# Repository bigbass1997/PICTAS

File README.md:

### Description
The PICTAS is an input device used to replay Tool-Assisted-Speedruns (aka Tool-Assisted-Superruns) on physical hardware.

A PIC18F47K42 microcontroller is used for the replay portion of the device, and the smaller PIC18F27K42 is used for controlling the input displays.

Unlike a typical TAS replay device, this one stores the TAS inputs on-board, using serial flash memory (W25Q128JVSIQ), capable of storing 16 MB of input data. The advantage is that USB communication is not required during replay. It simplifies the replay process, and greatly reduces the chance of corrupted inputs. Additionally, once programmed, the device can be used without a USB host computer (WIP feature).

This project is still a prototype under heavy development. While I will offer help and support as best I can, please understand that significant code and design changes can occur at any time.

### Usage
The general process looks like this: Load movie into a [host interface](https://github.com/bigbass1997/pictas-interface-rs). Program the movie's inputs and config options onto the PICTAS device. Finally, use one of the available start methods to begin the playback.

Refer to the [PICTAS-Interface project](https://github.com/bigbass1997/pictas-interface-rs) for details on how to use that software. Anyone is free to make their own interface software. There will be docs provided here once the communication protocol has stablized. The PICTAS communicates over USB at a 500,000 baud rate. Single byte commands are initiated from the interface. The PICTAS will respond with one or more bytes.

Because the input data is saved onto the device, you will _not_ need to reprogram it again unless you wish to change the TAS inputs or other configuration data.

### Flash Memory Map
```
0x000000 - 0xFFEFFF | Sequential controller inputs
0xFFF000 - 0xFFF0FF | Config options
0xFFF100 - 0xFFFFFF | Frame-numbered commands
```
All except the last sector (4KB) of memory, is dedicated to storing the TAS inputs. Format will depend on the console and how many controllers are used. Within the last sector, the first 256 bytes are for config options, while the rest is for special commands that are performed on specific frame numbers.

Each command is made up of a 3 byte wide number, which specifies the frame number. And then a 1 byte command.
```
0x00 | Console Reset
0x01 | Console Power off and on

0xFF | Null
```

### Input Displays
This replay device also supports input displays (aka viz/visualization boards), providing the viewers a way see which inputs are being pressed in real time.

The displays are designed to be placed on a SPI bus, where each display board shares the same clock and serial signals. Each device uses it's own Chip Select signal as a data latch.

An auxilary power supply must be connected for these displays. The PCB design is rated for a maximum of 2Amps.

### Discord/Support
If you have questions or suggestions, you can find me on the [N64brew Discord server](https://discord.gg/WqFgNWf) or the [TASBot server](https://discord.tas.bot/).

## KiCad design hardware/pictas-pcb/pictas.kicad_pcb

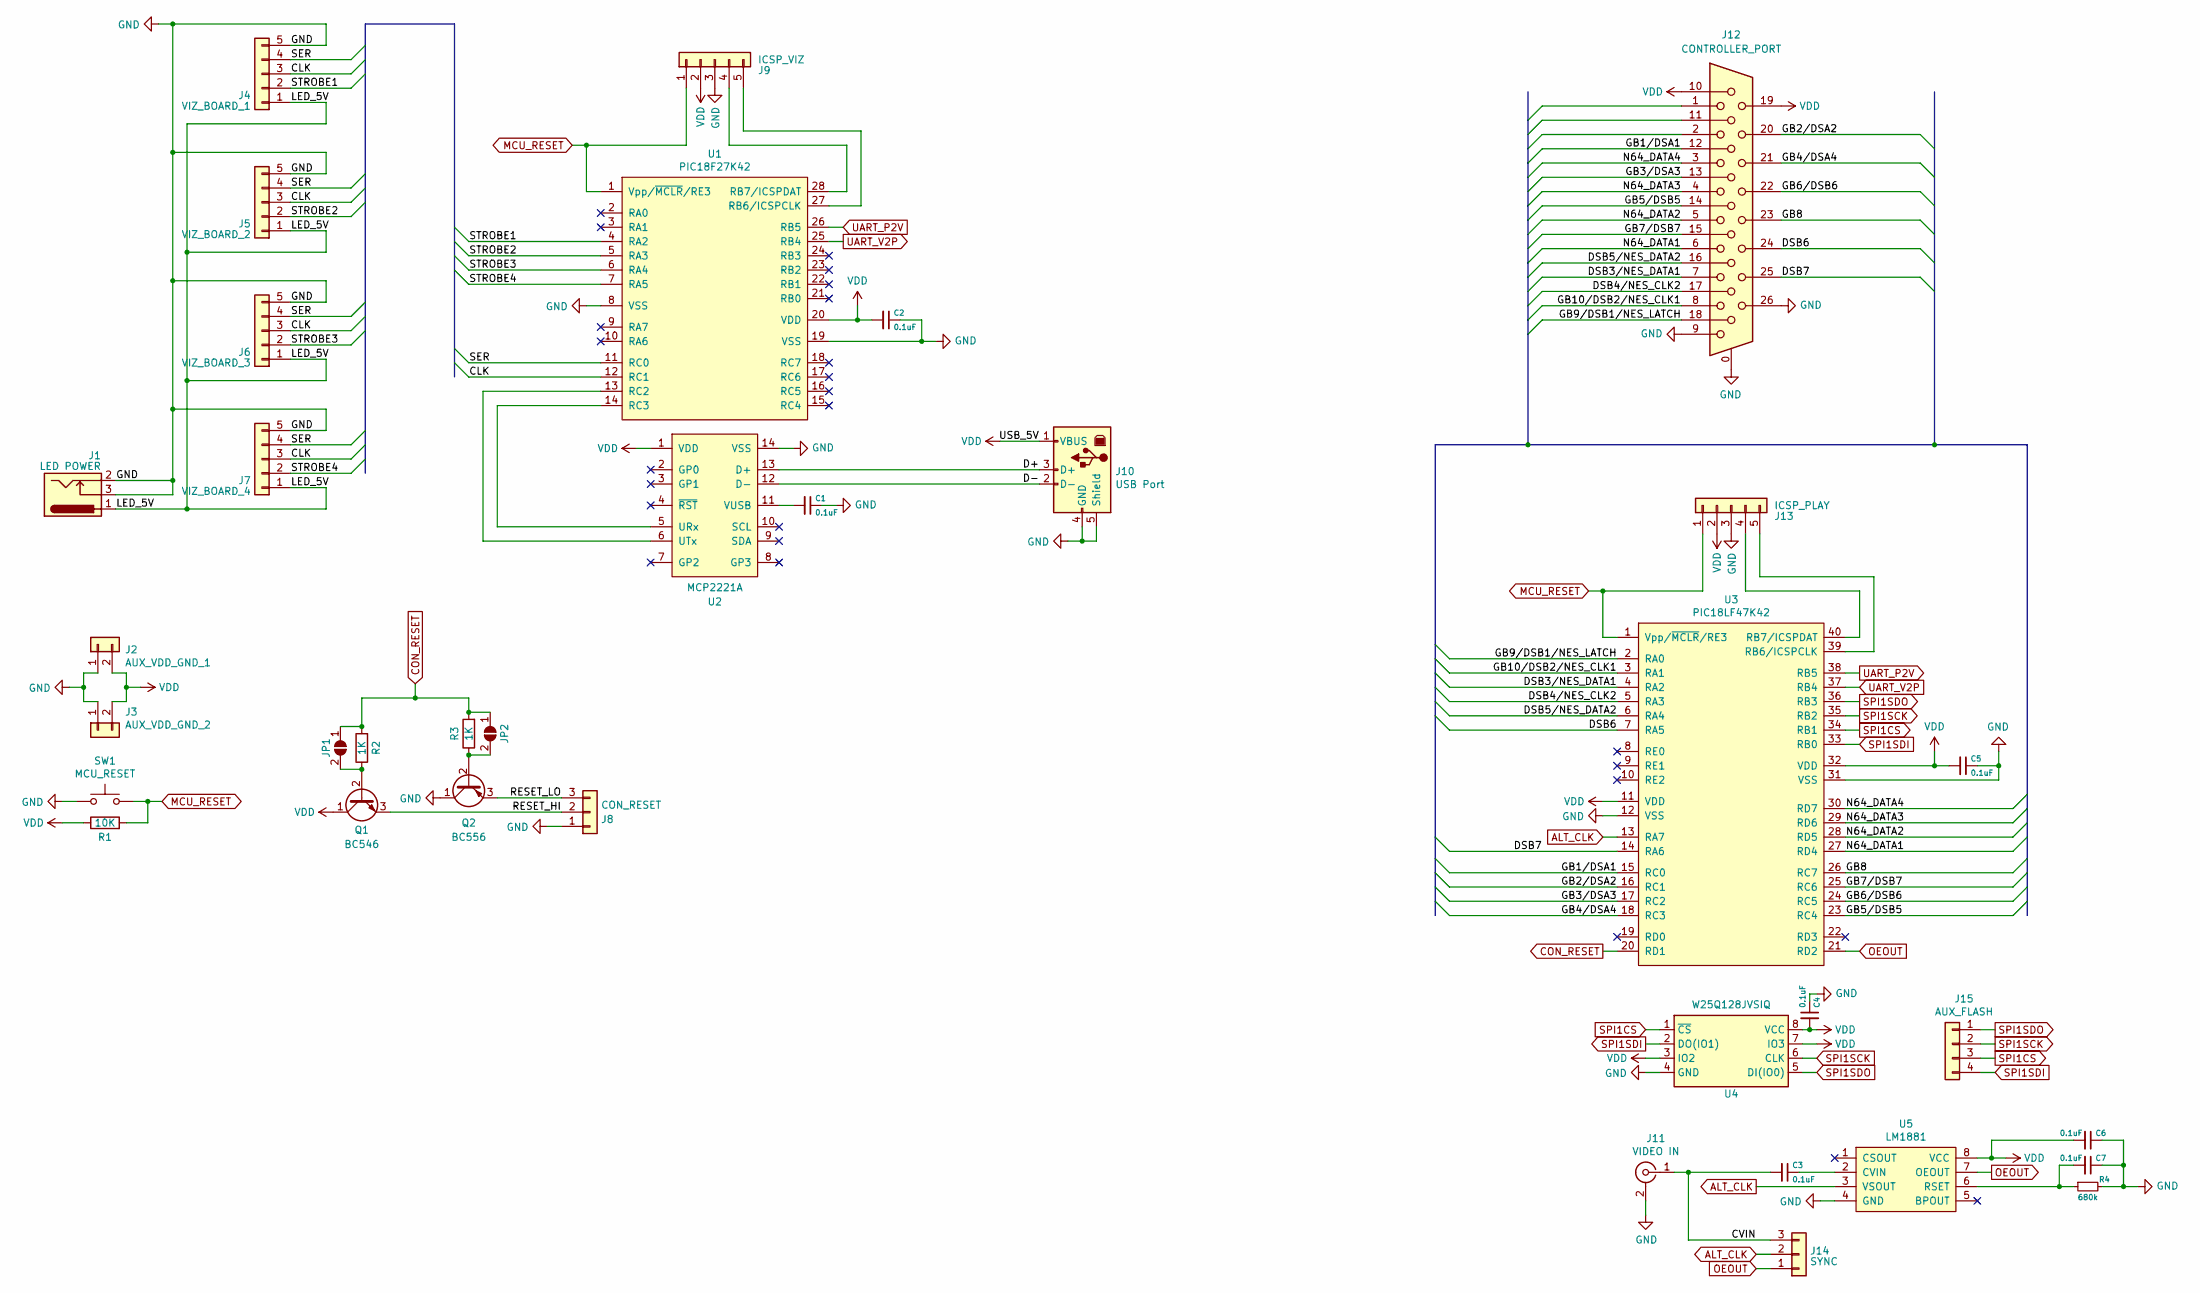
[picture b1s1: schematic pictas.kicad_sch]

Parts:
C1, C2, C3, C4, C5, C6, C7: 0.1uF; C_Disc_D3.4mm_W2.1mm_P2.50mm
J1: LED POWER; BarrelJack_Horizontal
J2: AUX_VDD_GND_1; PinHeader_1x02_P2.54mm_Vertical
J3: AUX_VDD_GND_2; PinSocket_1x02_P2.54mm_Vertical
J4: VIZ_BOARD_1; PinHeader_1x05_P2.54mm_Horizontal
J5: VIZ_BOARD_2; PinHeader_1x05_P2.54mm_Horizontal
J6: VIZ_BOARD_3; PinHeader_1x05_P2.54mm_Horizontal
J7: VIZ_BOARD_4; PinHeader_1x05_P2.54mm_Horizontal
J8: CON_RESET; PinHeader_1x03_P2.54mm_Horizontal
J9: ICSP_VIZ; PinSocket_1x05_P2.54mm_Horizontal
J10: USB Port; USB_B_OST_USB-B1HSxx_Horizontal
J11: VIDEO IN; PJRAN1X1U04X
J12: CONTROLLER_PORT; L77HDA26SD1CH4R
J13: ICSP_PLAY; PinSocket_1x05_P2.54mm_Horizontal
J14: SYNC; PinHeader_1x03_P2.54mm_Horizontal
J15: AUX_FLASH; PinHeader_1x04_P2.54mm_Vertical
JP1, JP2: SolderJumper_2_Open; SolderJumper-2_P1.3mm_Open_TrianglePad1.0x1.5mm
Q1: BC546; TO-92_Inline
Q2: BC556; TO-92_Inline
R1: 10K; R_Axial_DIN0207_L6.3mm_D2.5mm_P10.16mm_Horizontal
R2, R3: 1K; R_Axial_DIN0207_L6.3mm_D2.5mm_P10.16mm_Horizontal
R4: 680k; R_Axial_DIN0207_L6.3mm_D2.5mm_P10.16mm_Horizontal
SW1: MCU_RESET; SW_PUSH_6mm_H7.3mm
U1: PIC18F27K42; DIP-28_W7.62mm
U2: MCP2221A; DIP-14_W7.62mm
U3: PIC18LF47K42; DIP-40_W15.24mm
U4: W25Q128JVSIQ; SOIC-8_5.275x5.275mm_P1.27mm
U5: LM1881; SOIC-8_3.9x4.9mm_P1.27mm

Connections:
/CLK: J4.3, J5.3, J6.3, J7.3, U1.12 (RC1)
/CVIN: C3.2, J11.1 (In), J14.3
/D+: J10.3 (D+), U2.13 (D+)
/D-: J10.2 (D-), U2.12 (D-)
/DSB3/NES_DATA1: J12.7, U3.4 (RA2)
/DSB4/NES_CLK2: J12.17, U3.5 (RA3)
/DSB5/NES_DATA2: J12.16, U3.6 (RA4)
/DSB6: J12.24, U3.7 (RA5)
/DSB7: J12.25, U3.14 (RA6)
/GB1/DSA1: J12.12, U3.15 (RC0)
/GB2/DSA2: J12.20, U3.16 (RC1)
/GB3/DSA3: J12.13, U3.17 (RC2)
/GB4/DSA4: J12.21, U3.18 (RC3)
/GB5/DSB5: J12.14, U3.23 (RC4)
/GB6/DSB6: J12.22, U3.24 (RC5)
/GB7/DSB7: J12.15, U3.25 (RC6)
/GB8: J12.23, U3.26 (RC7)
/GB9/DSB1/NES_LATCH: J12.18, U3.2 (RA0)
/GB10/DSB2/NES_CLK1: J12.8, U3.3 (RA1)
/LED_5V: J1.1, J4.1, J5.1, J6.1, J7.1
/N64_DATA1: J12.6, U3.27 (RD4)
/N64_DATA2: J12.5, U3.28 (RD5)
/N64_DATA3: J12.4, U3.29 (RD6)
/N64_DATA4: J12.3, U3.30 (RD7)
/RESET_HI: J8.2, Q1.3 (E)
/RESET_LO: J8.3, Q2.3 (E)
/SER: J4.4, J5.4, J6.4, J7.4, U1.11 (RC0)
/STROBE1: J4.2, U1.4 (RA2)
/STROBE2: J5.2, U1.5 (RA3)
/STROBE3: J6.2, U1.6 (RA4)
/STROBE4: J7.2, U1.7 (RA5)
ALT_CLK: J14.2, U3.13 (RA7), U5.3 (VSOUT)
CON_RESET: JP1.1 (A), JP2.1 (A), R2.2, R3.2, U3.20 (RD1)
GND: C1.1, C2.1, C4.1, C5.1, C6.1, C7.1, J1.2, J1.3, J2.1, J3.1, J4.5, J5.5, J6.5, J7.5, J8.1, J9.3, J10.4 (GND), J10.5 (Shield), J11.2 (Ext), J12.0, J12.9, J12.26, J13.3, Q2.1 (C), R4.2, SW1.1, U1.8 (VSS), U1.19 (VSS), U2.14 (VSS), U3.12 (VSS), U3.31 (VSS), U4.4 (GND), U5.4 (GND)
MCU_RESET: J9.1, J13.1, R1.2, SW1.2, U1.1 (Vpp/~MCLR/RE3), U3.1 (Vpp/~MCLR/RE3)
unnamed: C1.2, U2.11 (VUSB)
unnamed: C3.1, U5.2 (CVIN)
unnamed: C7.2, R4.1, U5.6 (RSET)
unnamed: J9.4, U1.28 (RB7/ICSPDAT)
unnamed: J9.5, U1.27 (RB6/ICSPCLK)
unnamed: J13.4, U3.40 (RB7/ICSPDAT)
unnamed: J13.5, U3.39 (RB6/ICSPCLK)
unnamed: JP1.2 (B), Q1.2 (B), R2.1
unnamed: JP2.2 (B), Q2.2 (B), R3.1
unnamed: U1.13 (RC2), U2.6 (UTx)
unnamed: U1.14 (RC3), U2.5 (URx)
OEOUT: J14.1, U3.21 (RD2), U5.7 (OEOUT)
SPI1CS: J15.3, U3.34 (RB1), U4.1 (~CS)
SPI1SCK: J15.2, U3.35 (RB2), U4.6 (CLK)
SPI1SDI: J15.4, U3.33 (RB0), U4.2 (DO(IO1))
SPI1SDO: J15.1, U3.36 (RB3), U4.5 (DI(IO0))
UART_P2V: U1.26 (RB5), U3.38 (RB5)
UART_V2P: U1.25 (RB4), U3.37 (RB4)
VDD: C2.2, C4.2, C5.2, C6.2, J2.2, J3.2, J9.2, J10.1 (VBUS), J12.10, J12.19, J13.2, Q1.1 (C), R1.1, U1.20 (VDD), U2.1 (VDD), U3.11 (VDD), U3.32 (VDD), U4.3 (IO2), U4.7 (IO3), U4.8 (VCC), U5.8 (VCC)

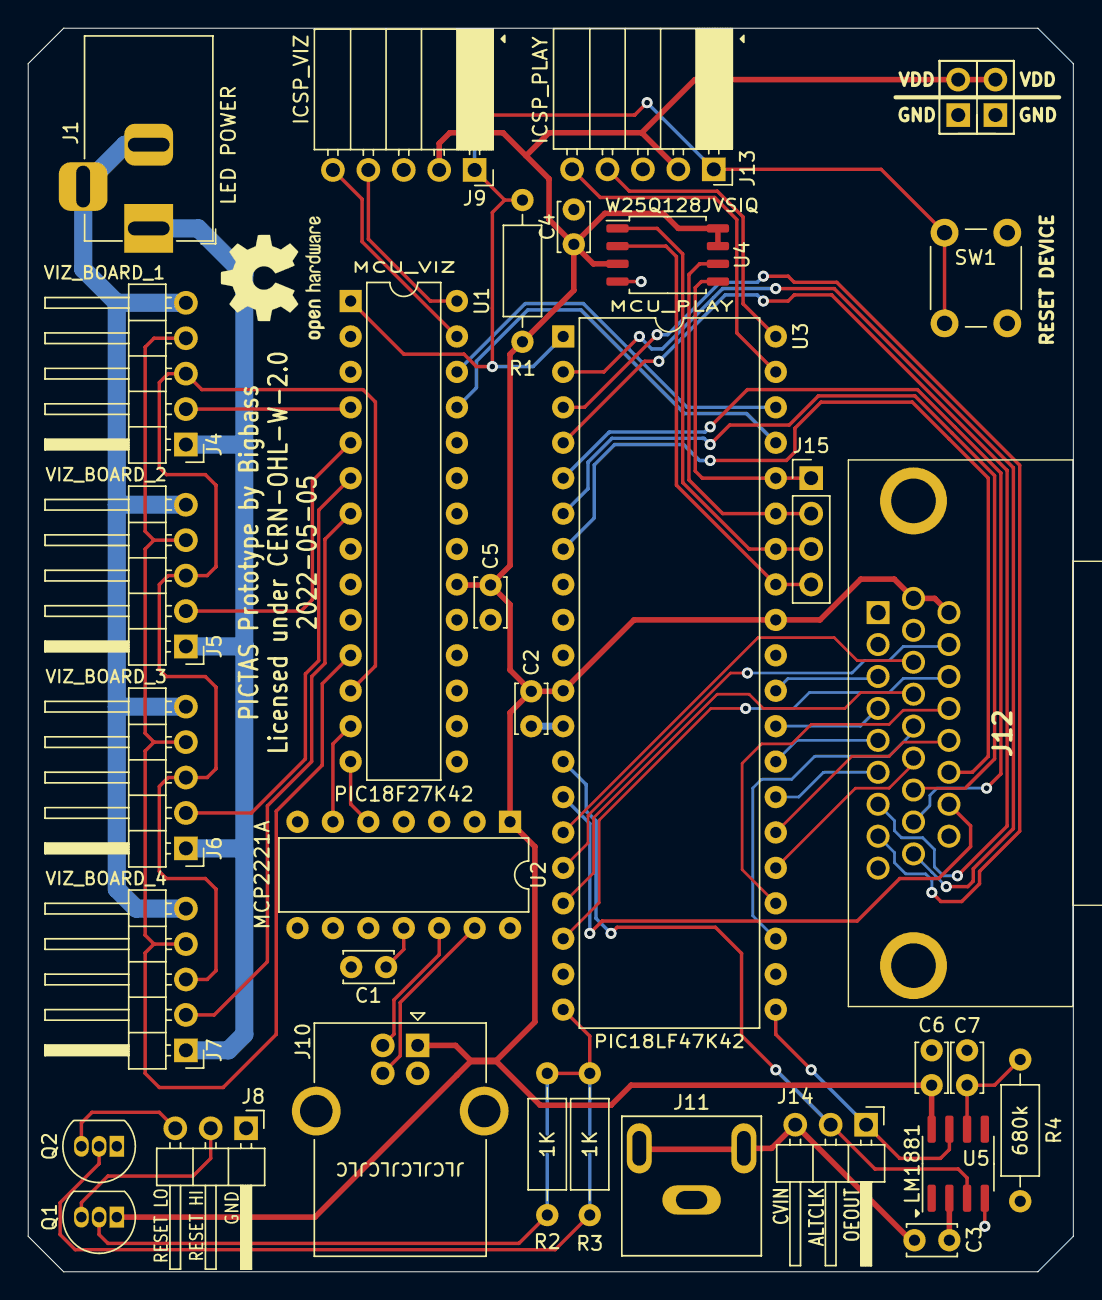
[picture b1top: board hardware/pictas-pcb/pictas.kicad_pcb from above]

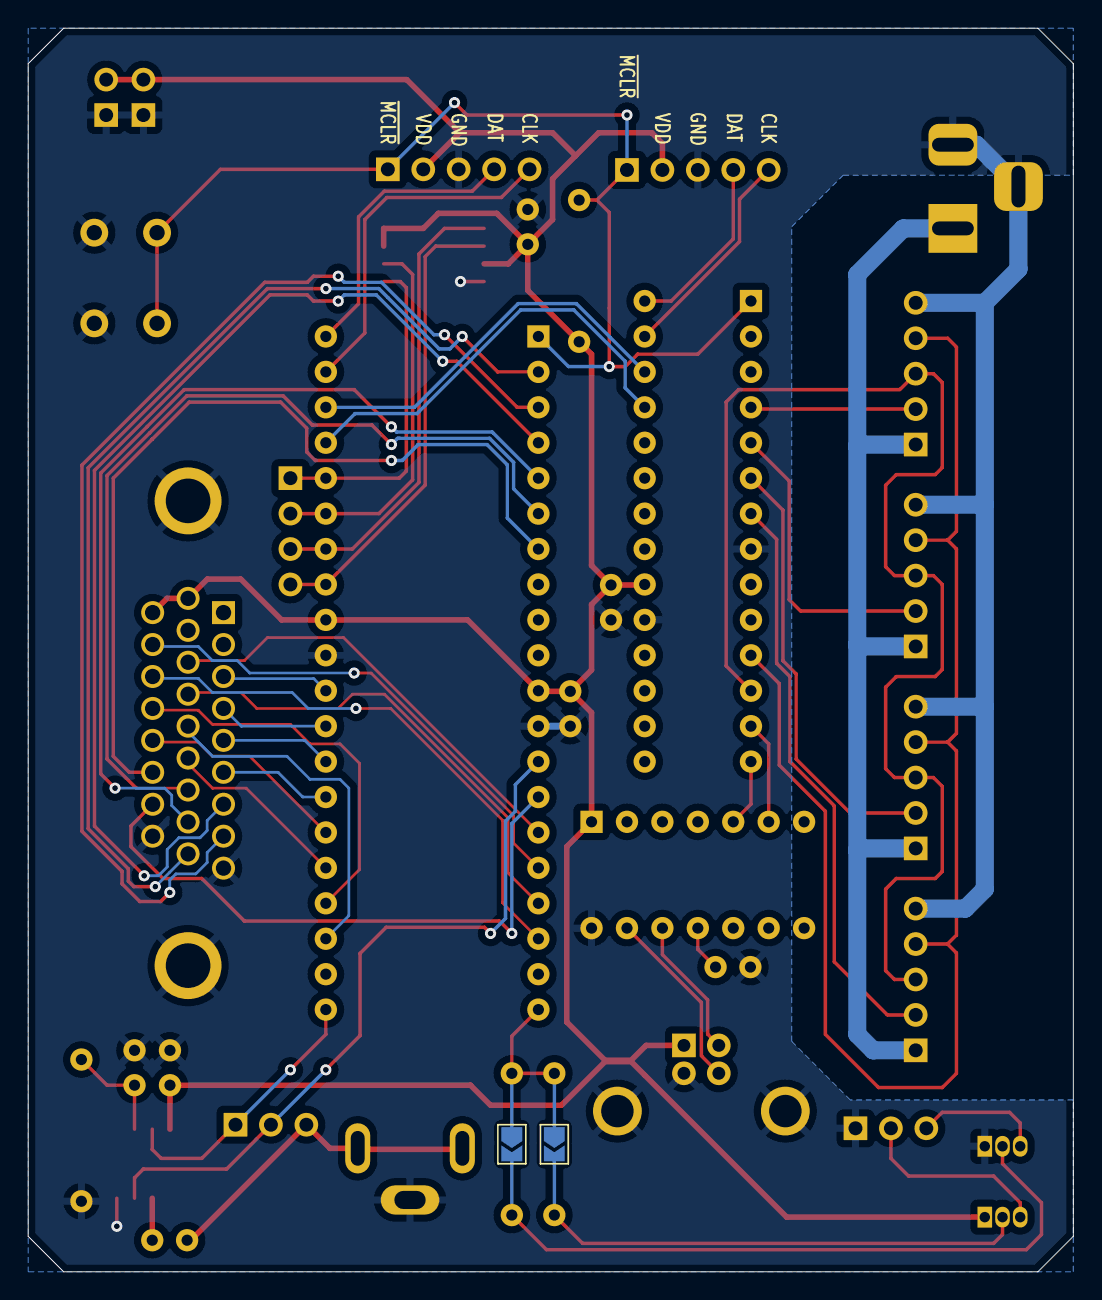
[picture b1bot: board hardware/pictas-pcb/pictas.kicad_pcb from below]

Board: 2 copper layers, 74.9 x 89.2 mm, 36 parts (2 on the bottom side), 54 nets.

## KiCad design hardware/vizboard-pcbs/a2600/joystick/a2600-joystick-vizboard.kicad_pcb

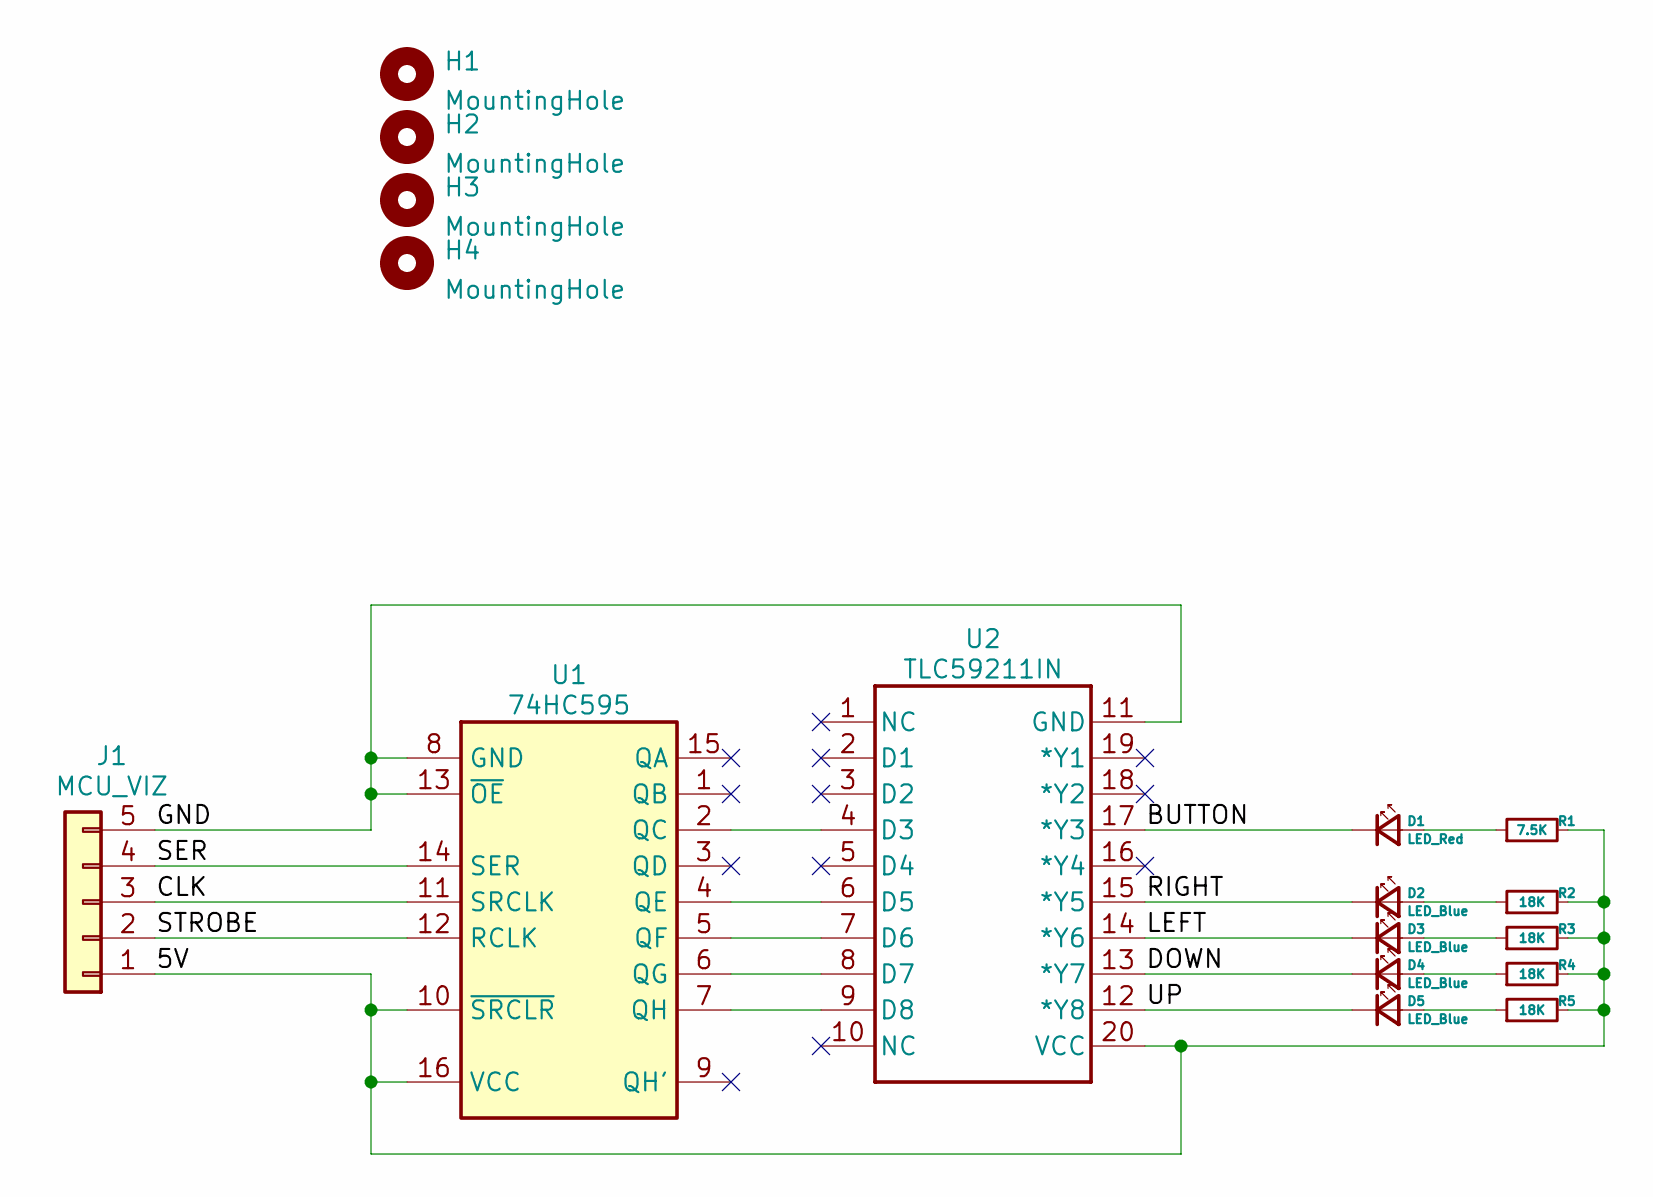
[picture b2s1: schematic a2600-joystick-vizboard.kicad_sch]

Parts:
D1: LED_Red; LED_D5.0mm
D2, D3, D4, D5: LED_Blue; LED_D5.0mm
H1, H2, H3, H4: MountingHole; MountingHole_3.2mm_M3
J1: MCU_VIZ; PinHeader_1x05_P2.54mm_Horizontal
R1: 7.5K; R_Axial_DIN0207_L6.3mm_D2.5mm_P10.16mm_Horizontal
R2, R3, R4, R5: 18K; R_Axial_DIN0207_L6.3mm_D2.5mm_P10.16mm_Horizontal
U1: 74HC595; DIP-16_W7.62mm
U2: TLC59211IN; DIP-20_W7.62mm

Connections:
/5V: J1.1, R1.2, R2.2, R3.2, R4.2, R5.2, U1.10 (~SRCLR), U1.16 (VCC), U2.20 (VCC)
/BUTTON: D1.1 (K), U2.17 (*Y3)
/CLK: J1.3, U1.11 (SRCLK)
/DOWN: D4.1 (K), U2.13 (*Y7)
/GND: J1.5, U1.8 (GND), U1.13 (~OE), U2.11 (GND)
/LEFT: D3.1 (K), U2.14 (*Y6)
/RIGHT: D2.1 (K), U2.15 (*Y5)
/SER: J1.4, U1.14 (SER)
/STROBE: J1.2, U1.12 (RCLK)
/UP: D5.1 (K), U2.12 (*Y8)
unnamed: D1.2 (A), R1.1
unnamed: D2.2 (A), R2.1
unnamed: D3.2 (A), R3.1
unnamed: D4.2 (A), R4.1
unnamed: D5.2 (A), R5.1
unnamed: U1.2 (QC), U2.4 (D3)
unnamed: U1.4 (QE), U2.6 (D5)
unnamed: U1.5 (QF), U2.7 (D6)
unnamed: U1.6 (QG), U2.8 (D7)
unnamed: U1.7 (QH), U2.9 (D8)

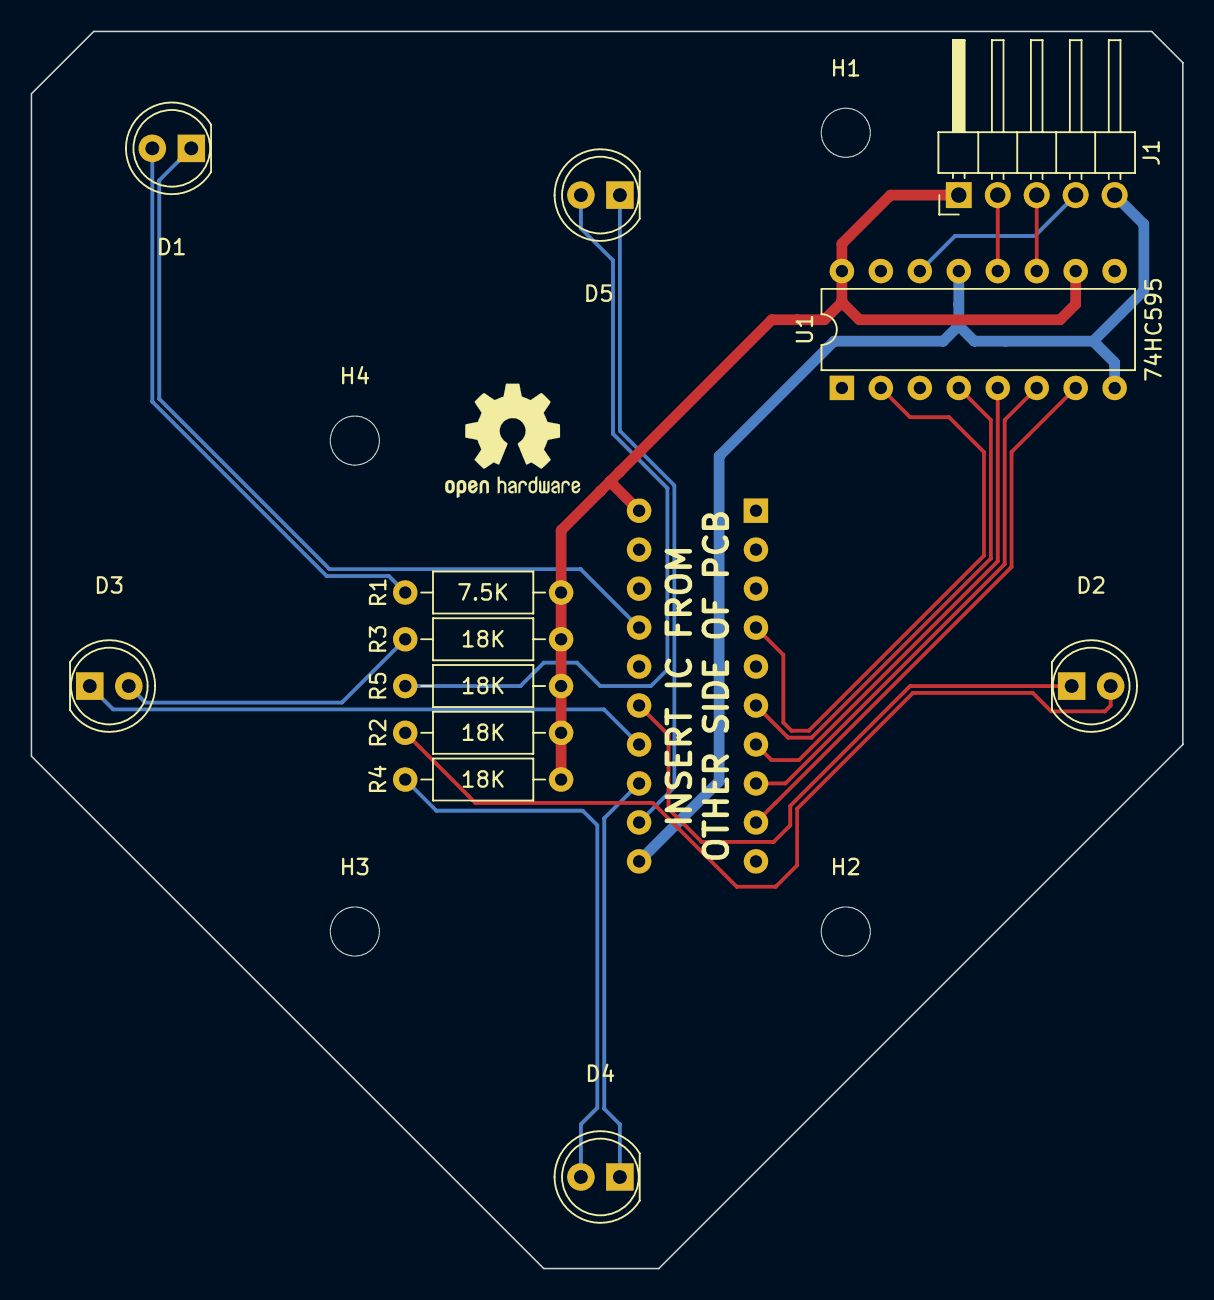
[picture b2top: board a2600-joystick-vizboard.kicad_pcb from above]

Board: 2 copper layers, 75.1 x 80.6 mm, 17 parts (1 on the bottom side), 20 nets.

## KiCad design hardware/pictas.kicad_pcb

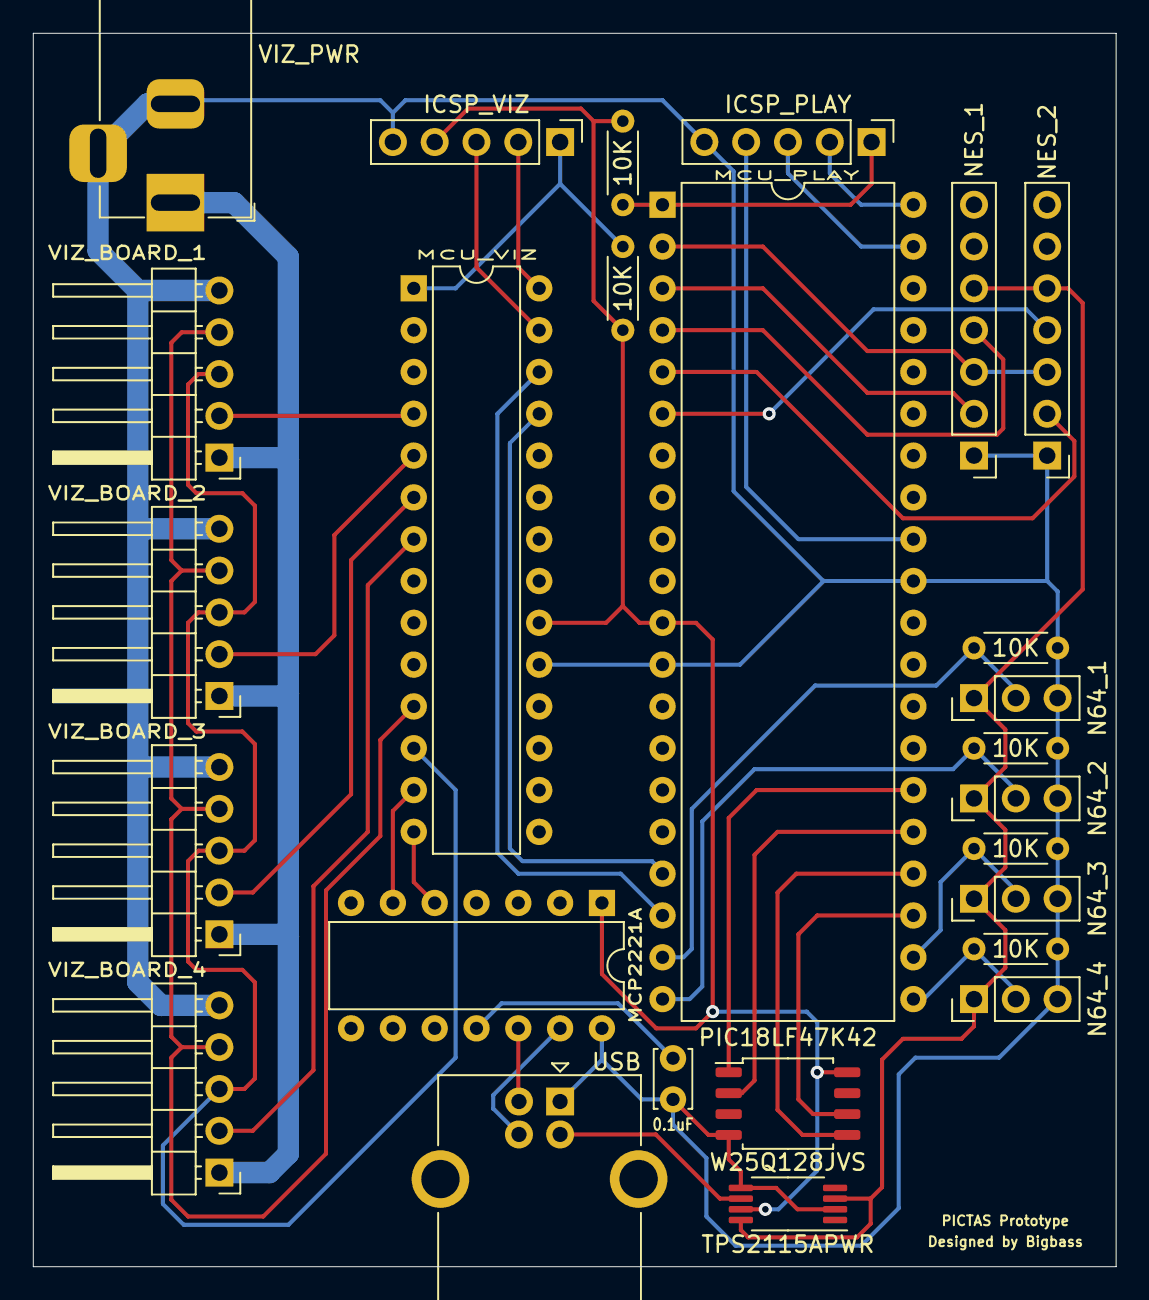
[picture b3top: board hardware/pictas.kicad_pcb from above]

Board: 2 copper layers, 65.8 x 74.9 mm, 26 parts (0 on the bottom side), 38 nets.

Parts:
0.1uF: 0.1uF; C_Disc_D3.4mm_W2.1mm_P2.50mm
10K: 10K; R_Axial_DIN0204_L3.6mm_D1.6mm_P5.08mm_Horizontal
10K#2, 10K#3, 10K#4, 10K#5, 10K#6: 10k; R_Axial_DIN0204_L3.6mm_D1.6mm_P5.08mm_Horizontal
ICSP_PLAY: ICSP_PLAY; PinHeader_1x05_P2.54mm_Vertical
ICSP_VIZ: ICSP_VIZ; PinHeader_1x05_P2.54mm_Vertical
MCP2221A: MCP2221A; DIP-14_W7.62mm
MCU_PLAY: PIC18LF47K42; DIP-40_W15.24mm
MCU_VIZ: PIC18F27K42; DIP-28_W7.62mm
N64_1: N64_CNT1; PinHeader_1x03_P2.54mm_Vertical
N64_2: N64_CNT2; PinHeader_1x03_P2.54mm_Vertical
N64_3: N64_CNT3; PinHeader_1x03_P2.54mm_Vertical
N64_4: N64_CNT4; PinHeader_1x03_P2.54mm_Vertical
NES_1: NES_CNT1; PinHeader_1x07_P2.54mm_Vertical
NES_2: NES_CNT2; PinHeader_1x07_P2.54mm_Vertical
TPS2115APWR: TPS2115APWR; TSSOP-8_4.4x3mm_P0.65mm
USB: USB Port; USB_B_OST_USB-B1HSxx_Horizontal
VIZ_BOARD_1: VizBoard0; PinHeader_1x05_P2.54mm_Horizontal
VIZ_BOARD_2: VizBoard1; PinHeader_1x05_P2.54mm_Horizontal
VIZ_BOARD_3: VizBoard2; PinHeader_1x05_P2.54mm_Horizontal
VIZ_BOARD_4: VizBoard3; PinHeader_1x05_P2.54mm_Horizontal
VIZ_PWR: LED_Power_Jack; BarrelJack_Horizontal
W25Q128JVS: W25Q128JVS; SOIC-8_5.275x5.275mm_P1.27mm

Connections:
/3.3V: N64_1.1, N64_2.1, N64_3.1, N64_4.1, NES_1.5, NES_2.5, TPS2115APWR.3, TPS2115APWR.8
/5V: VIZ_BOARD_1.1, VIZ_BOARD_2.1, VIZ_BOARD_3.1, VIZ_BOARD_4.1, VIZ_PWR.1
/CLK: MCU_VIZ.12, VIZ_BOARD_1.3, VIZ_BOARD_2.3, VIZ_BOARD_3.3, VIZ_BOARD_4.3
/D+: MCP2221A.12, USB.2
/D-: MCP2221A.13, USB.3
/GND: 0.1uF.1, 10K#3.1, 10K#4.1, 10K#5.1, 10K#6.1, ICSP_PLAY.5, ICSP_VIZ.5, MCP2221A.14, MCU_PLAY.12, MCU_PLAY.31, MCU_VIZ.19, N64_1.3, N64_2.3, N64_3.3, N64_4.3, NES_1.1, NES_2.1, TPS2115APWR.2, TPS2115APWR.5, USB.1, VIZ_BOARD_1.5, VIZ_BOARD_2.5, VIZ_BOARD_3.5, VIZ_BOARD_4.5, VIZ_PWR.2, VIZ_PWR.3, W25Q128JVS.4
/N64_DATA1: 10K#6.2, MCU_PLAY.19, N64_1.2
/N64_DATA2: 10K#5.2, MCU_PLAY.20, N64_2.2
/N64_DATA3: 10K#4.2, MCU_PLAY.22, N64_3.2
/N64_DATA4: 10K#3.2, MCU_PLAY.21, N64_4.2
/NES_CLK1: MCU_PLAY.3, NES_1.2
/NES_CLK2: MCU_PLAY.5, NES_2.2
/NES_DATA1: MCU_PLAY.4, NES_1.4
/NES_DATA2: MCU_PLAY.6, NES_2.4
/NES_LATCH: MCU_PLAY.2, NES_1.3, NES_2.3
/Power Select/OUT_PWR: 10K.2, 10K#2.2, ICSP_VIZ.4, MCP2221A.1, MCU_PLAY.11, MCU_VIZ.20, TPS2115APWR.7, W25Q128JVS.8
/SER: MCU_VIZ.11, VIZ_BOARD_1.4, VIZ_BOARD_2.4, VIZ_BOARD_3.4, VIZ_BOARD_4.4
/SPI1SCK: MCU_PLAY.23, W25Q128JVS.6
/SPI1SDI: MCU_PLAY.24, W25Q128JVS.5
/SPI1SDO: MCU_PLAY.25, W25Q128JVS.2
/STROBE0: MCU_VIZ.4, VIZ_BOARD_1.2
/STROBE1: MCU_VIZ.5, VIZ_BOARD_2.2
/STROBE2: MCU_VIZ.6, VIZ_BOARD_3.2
/STROBE3: MCU_VIZ.7, VIZ_BOARD_4.2
/UART-->: MCU_PLAY.17, MCU_VIZ.25
/UART<--: MCU_PLAY.18, MCU_VIZ.26
/USB_5V: TPS2115APWR.6, USB.4
/~CS: MCU_PLAY.26, W25Q128JVS.1
unnamed: 0.1uF.2, MCP2221A.11
unnamed: 10K#2.1, ICSP_PLAY.1, MCU_PLAY.1
unnamed: ICSP_PLAY.2, MCU_PLAY.40
unnamed: ICSP_PLAY.3, MCU_PLAY.39
unnamed: ICSP_PLAY.4, MCU_PLAY.32
unnamed: 10K.1, ICSP_VIZ.1, MCU_VIZ.1
unnamed: ICSP_VIZ.2, MCU_VIZ.28
unnamed: ICSP_VIZ.3, MCU_VIZ.27
unnamed: MCP2221A.6, MCU_VIZ.13
unnamed: MCP2221A.5, MCU_VIZ.14

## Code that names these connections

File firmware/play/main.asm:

    include "p18f47k42.inc"
    include "macros.inc"
    processor 18f47k42
    
    CONFIG WDTE = OFF
   ; CONFIG DEBUG = ON
    CONFIG LVP = ON
    CONFIG MCLRE = EXTMCLR
    CONFIG MVECEN = ON ; Eanbles Interrupt Vector Table ; IVTBASE + 2*(vector number)
    
    CONFIG RSTOSC = HFINTOSC_64MHZ
    CONFIG FEXTOSC = OFF
    CONFIG CLKOUTEN = OFF
    
    CONFIG XINST = ON
    
ResVec      code	0x0000
    goto    Setup
    
IOCVec	    code	0x0016	; (0x0008 + (2 * 7))
    dw	    (0x0100>>2)
    
INT0Vec	    code	0x0018	; (0x0008 + (2 * 8))
    dw	    (0x0300>>2)
    
TMR0Vec	    code	0x0046	; (0x0008 + (2 * 31))
    dw	    (0x0500>>2)
    
U1RXVec	    code	0x003E	; (0x0008 + (2 * 27))
    dw	    (0x0600>>2)
    
	    code	0x1000
; === Look at bottom of file for ISR routines ===
    
; === DEFINE PINS (text substitutions) ===
; refer to pinout documentation for more information
; reminder: all button input pins should be pulled-DOWN (default state is cleared aka 0)
;           connect pin to power to set button to a "pressed" state
#define	    PIN_NES_DATA2	LATA,  4
#define	    PIN_NES_CLK2	PORTA, 3

#define	    PIN_NES_DATA1	LATA,  2
#define	    PIN_NES_CLK1	PORTA, 1

#define	    PIN_NES_LATCH	PORTA, 0    ; Latch pins for each controller are connected at console-level

#define     PIN_FLASH_CS        LATB,  1
#define	    PIN_FLASH_CS_RD	PORTB, 1    ; Used to check what the last set state was

#define	    PIN_UART_HOST	LATE,  2    ; Signal to MCU_Viz whether to write UART to host or not

#define     PIN_N64_DATAIN      PORTD, 4
#define     PIN_N64_DATAOUT     LATD,  4    ; LAT register is used for writing data out
#define     TRIS_N64_DATA       TRISD, 4

#define	    PIN_STAT_LED	LATD,  0    ; Status LED indicator
#define	    PIN_CON_RESET	LATD,  1


; === REGISTERS ===
; ACCESS BANK  (0x00 - 0x5F)
ZEROS_REG       equ H'00' ; Always 0x00
ONES_REG        equ H'01' ; Always 0xFF

N64_BIT_REG     equ H'02' ; This register is used to temporarily store 3-4us of data
                          ; to determine if the data recieved is a 0 or 1 or a stop bit.
N64_CMD_REG     equ H'03'

; 0x04 - 0x07 unused

N64_STATE_REG1  equ H'08' ; Buffer:  Button states
N64_STATE_REG2  equ H'09' ; Buffer:  Button states
N64_STATE_REG3  equ H'0A' ; Buffer:  Analog Stick X-Axis ; -127 to +128
N64_STATE_REG4  equ H'0B' ; Buffer:  Analog Stick Y-Axis ; -127 to +128

TX_DATA         equ H'0C' ; Alias for TX_DATA1
TX_DATA1        equ H'0C' ; Data to be transmitted to the console
TX_DATA2        equ H'0D' ; Data to be transmitted to the console, used as "double buffer"

UTIL_FLAGS      equ H'0E' ; Utility Flags, initalized with 0x00
; <7> If set, determined byte is invalid, decoding should halt
; <6> If set, no new NES latches should be accepted
; <5> If set, a TAS replay is in progress
; <4> Used by FlashLoadNextEvent to store previous PIN_FLASH_CS state
; <3> If set, reset NES on next latch
; <2> If set, A2600/Gen vsync has occured; is cleared once A2600/Gen loop has acknowledge this
; <1:0> Unused

; Pause Clock
PAUSE_REG_0     equ H'10'
PAUSE_REG_1     equ H'11'
PAUSE_REG_2     equ H'12'

PAUSE_TMP_0     equ H'13'
PAUSE_TMP_1     equ H'14'
PAUSE_TMP_2     equ H'15'

; Auxillary Loop Counters
LOOP_COUNT_0    equ H'16'
LOOP_COUNT_1    equ H'17'

; FLASH Pointers
FLASH_ADDR_HIGH equ H'18'
FLASH_ADDR_MID  equ H'19'
FLASH_ADDR_LOW  equ H'1A'

FLASH_LAST_HIGH	equ H'1B'
FLASH_LAST_MID	equ H'1C'
FLASH_LAST_LOW	equ H'1D'

FLASH_EVENT_MID equ H'1E'
FLASH_EVENT_LOW equ H'1F'

; NES Controller Data
NES_STATE_REG1	equ H'20'
NES_STATE_REG2	equ H'21'
NES_STATE_TMP1	equ H'22'
NES_STATE_TMP2	equ H'23'

; InterUART Protocol Constants
MCUCMD_HOST	equ H'24'   ; init to 0x01
MCUCMD_SHOW8_0	equ H'25'   ; init to 0xD0
MCUCMD_SHOW8_1	equ H'26'   ; init to 0xD1
MCUCMD_SHOW8_2	equ H'27'   ; init to 0xD2
MCUCMD_SHOW8_3	equ H'28'   ; init to 0xD3

; A2600 Frame State Data
A2600_STATE_REG1    equ	H'29'
A2600_STATE_REG2    equ H'2A'
A2600_STATE_REG3    equ H'2B'

GEN_STATE_REG1	equ H'2C'
GEN_STATE_REG2	equ H'2D'

; 0x2E - 0x56 unused

LAST_USB_BYTE	equ H'57'

CFG_EVENT_HIGH	equ H'58'
CFG_EVENT_MID	equ H'59'
CFG_EVENT_LOW	equ H'5A'
CFG_EVENT_CMD	equ H'5B'

CUR_INPUT_HIGH	equ H'5C'
CUR_INPUT_MID	equ H'5D'
CUR_INPUT_LOW	equ H'5E'   ; keeps track of the current input frame

JUNK_REG        equ H'5F'

; BANK 0  (0x60 - 0xFF)
; These bytes are used for temporary storage of data coming from or going to the N64 console.
; While only 4 addresses are defined, this whole section of memory is dedicated for this purpose.
; Remember to specify in every instruction to use the BSR instead of Access memory.
N64_DATA_DETER  equ H'60'
N64_DATA_TMP0   equ H'61'
N64_DATA_TMP1   equ H'62'
N64_DATA_TMP2   equ H'63'
N64_DATA_TMP3   equ H'64'

; BANK 1
; This bank is used when writing a 256 byte sector of data to the FLASH memory

; BANK 2
; Config options are stored here

; 0x00 - 0xFC unused

CFG_LASTF_HIGH	equ H'FD'
CFG_LASTF_MID	equ H'FE'
CFG_LASTF_LOW	equ H'FF'



; === CONSTANT BYTES ===
USB_CMD_PING        equ H'01'
USB_CMD_DUMP        equ H'02'
USB_CMD_RUN_N64     equ H'03'
USB_CMD_RUN_NES     equ H'04'
USB_CMD_RUNED_NES   equ H'05'
USB_CMD_RUNRST_NES  equ H'06'
USB_CMD_RUNMAN_NES  equ H'07'
USB_CMD_RUN_A2600   equ H'08'
USB_CMD_RUN_GEN	    equ H'09'
USB_CMD_PROGTAS     equ H'AA'
USB_CMD_PROGCFG     equ H'AB'
USB_CMD_RESETMCU    equ H'AE'

N64_CMD_RESET       equ H'FF'
N64_CMD_INFO        equ H'00'
N64_CMD_STATE       equ H'01'
N64_CMD_READACCES   equ H'02' ; unimplemented
N64_CMD_WRITEACCES  equ H'03' ; unimplemented

; https://n64brew.dev/wiki/Joybus_Protocol
N64_BIT_ZERO    equ B'11110001'
N64_BIT_ONE     equ B'11110111'
N64_BIT_CONSSTP equ B'11110111' ; bit <0> is not technically used, but for ease of programming, it is set to 1
N64_BIT_CONTSTP equ B'11110011'

; COMMON SUBROUTINES (may also contain macros) ;
    include "sub-utilities.inc"
    include "sub-flash.inc"
    
; Initialize device ;
Setup:
    include "setup.inc"
    
    movlb   B'000000'
    ;goto    GenesisMain ;;; DEBUG
    
;;;;;====================== Main Loop ======================;;;;;
MainLoop:
    
    goto    MainLoop
    
    
;;;;;====================== N64 Logic ======================;;;;;
    include "n64.inc"
    
    
;;;;;====================== NES Logic ======================;;;;;
    include "nes.inc"
    
    
;;;;;====================== A2600 Logic ======================;;;;;
    include "a2600.inc"
    
    
;;;;;====================== Genesis Logic ======================;;;;;
    include "genesis.inc"
    
    
    
; INTERRUPT SUBROUTINES ;
    
    include "isr.ioc.inc"
    include "isr.int0.inc"
    include "isr.tmr0.inc"
    include "isr.u1rx.inc"
    
    end

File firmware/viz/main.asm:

    include "p18f27k42.inc"
    processor 18f27k42
    
    CONFIG WDTE = OFF
   ; CONFIG DEBUG = ON
    CONFIG LVP = ON
    CONFIG MCLRE = EXTMCLR
    CONFIG MVECEN = ON ; Eanbles Interrupt Vector Table ; IVTBASE + 2*(vector number)
    
    CONFIG RSTOSC = HFINTOSC_64MHZ
    
    CONFIG XINST = ON
    
ResVec      code	0x0000
    goto    Setup
    
U1RXVec	    code	0x003E	; (0x0008 + (2 * 27))
    dw	    (0x0200>>2)
    
U2RXVec	    code	0x006C	; (0x0008 + (2 * 50))
    dw	    (0x0400>>2)
    
	    code	0x0600
; === Look at bottom of file for ISR routines ===
    
; === DEFINE PINS (text substitutions) ===
; refer to pinout documentation for more information
; reminder: all button input pins should be pulled-DOWN (default state is cleared aka 0)
;           connect pin to power to set button to a "pressed" state
#define	    PIN_STROBE3		LATA,  5
#define	    PIN_STROBE2		LATA,  4
#define	    PIN_STROBE1		LATA,  3
#define	    PIN_STROBE0		LATA,  2

; === REGISTERS ===
; ACCESS BANK  (0x00 - 0x5F)
ZEROS_REG       equ H'00' ; Always 0x00
ONES_REG        equ H'01' ; Always 0xFF

UTIL_FLAGS      equ H'02' ; Utility Flags, initalized with 0x00
; <7:0> Unused

; Pause Clock
PAUSE_REG_0     equ H'03'
PAUSE_REG_1     equ H'04'
PAUSE_REG_2     equ H'05'

PAUSE_TMP_0     equ H'06'
PAUSE_TMP_1     equ H'07'
PAUSE_TMP_2     equ H'08'

; Auxillary Loop Counters
LOOP_COUNT_0    equ H'09'
LOOP_COUNT_1    equ H'0A'

; 0x0B - 0x5E unused

TEMP_REG        equ H'5F'

; BANK 0  (0x60 - 0xFF)
; Unused

; BANK 1
; MCU-Play FIFO Buffer
; Data received from MCU-Play will be stored here.
; FIFO is naive. It has a pointer and a size.
; If size > 255, it will wrap to zero. Buffer should never be this large though.


; === CONSTANT BYTES ===
MCUCMD_HOST	equ H'01'   ; Send the next byte to host

MCUCMD_SHOW8_BASE   equ H'D0'
MCUCMD_SHOW8_0	equ H'D0'   ; Send the next byte to SPI bus and strobe #0
MCUCMD_SHOW8_1	equ H'D1'   ; Send the next byte to SPI bus and strobe #1
MCUCMD_SHOW8_2	equ H'D2'   ; Send the next byte to SPI bus and strobe #2
MCUCMD_SHOW8_3	equ H'D3'   ; Send the next byte to SPI bus and strobe #3

; === SUBROUTINE & MACRO INCLUDES === ;
    include "macros.inc"
    include "sub-utilities.inc"

Setup:
    include "startup.inc"
    
    movlb   B'000000'
    
    ;; debug start ;;
    ;clrf    LOOP_COUNT_0
    ;setf    PAUSE_REG_0
;Debug_LoopSPI:
    ;movf    LOOP_COUNT_0, W
    ;call    WriteSPI_BUS0
    ;call    Pause2D
    
    ;incfsz  LOOP_COUNT_0
    ;goto    Debug_LoopSPI
    
    clrf    WREG
    call    WriteSPI_BUS0
    call    WriteSPI_BUS1
    call    WriteSPI_BUS2
    call    WriteSPI_BUS3
    ;; debug end ;;
    
    
;;;;;====================== MAIN LOOP ======================;;;;;
Start:
    include "cmd-buffer.inc"
    
    goto    Start
    
    
    
;;;;;================ INTERRUPT SUBROUTINES ================;;;;;
U1RXISR	    code	0x0200	; Byte recieved from USB  (high priority)
    BANKSEL PIR3
U1RXISR_Retry:
    movffl  U1RXB, U2TXB ; relay bytes to MCU_Play
    
    btfsc   PIR3, U1RXIF
    goto    U1RXISR_Retry
    
    retfie  1
    
U2RXISR	    code	0x0400	; Byte recieved from MCU_Play  (low priority)
    BANKSEL PIR6
U2RXISR_Retry:
    movffl  U2RXB, POSTINC0
    movlw   D'1'
    movwf   FSR0H
    
    btfsc   PIR6, U2RXIF
    goto    U2RXISR_Retry
    
    bsf	    SHADCON, SHADLO
    movffl  WREG_SHAD, WREG
    bcf	    SHADCON, SHADLO
    movlb   B'000000'
    retfie  0
    
    end

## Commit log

2020-12-18 SPI with FLASH tests working
2020-12-19 Added USB commands and communication. Program command is broken!
2020-12-20 More work on USB commands. Programming doesn't appear to be completely working for large datasets (static maybe?)
2021-01-18 Commented out debugging line that skipped USB communication. Added debug line to send back the byte just received over USB for validation.
2021-01-31 Reimplemented 0xFF N64 command that was accidentally removed.
2021-01-31 Changed line endings for new linux dev environment
2021-02-18 Added NES support, nothing verified yet though.
2021-02-18 Sped up SPI communication for NES. Confirmed TAS replay worked with this firmware.
2021-02-21 Implemented latch filtering aka windowing. Extra latches will repeat frame data for games were the first latch isn't the true input. Implemented clock filtering (additional 2us hardcoded atm). Added 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
2021-02-25 Fixed major bug where inputs within the same frame would not repeat more than one additional time, even if latches occurred more than that.
2021-03-06 Work in progress PCB design
2021-03-06 Cleaned unused code and comments.
2021-03-09 Redesigned PCB. Better controller placement and added visualization board connectors.
2021-03-25 Moved USB and Startup sections to include files, and disabled NES input control until a TAS begins so that external controllers can be used in parallel.
2021-03-25 Added external TAS start button and added LED indicator.
2021-04-03 Added code to support Everdrive start-ups, but it doesn't work quite as intended. Committing still as it provides framework, and still does allow starting from everdrive if the appropriate number of 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
2021-04-04 Added automatic NES reset capability
2021-04-16 Created new firmware project for visualization and USB microcontroller. Reorganized firmware directory.
2021-04-21 Updated schematic and prototype PCB design.
2021-04-22 Major overhaul to visual input display feature.
2021-06-17 Added reprogrammable config space in FLASH and changed how console resets are handled.
2021-06-19 Fixed address and XOR bugs in reset command handling.
2021-06-19 Fixed reset handling (previous commit was very broken)
2021-06-19 Removed debugging code
2021-06-20 Fixed timing bug where the MCU was operating too low after the latch pulse.
2021-06-27 Temporary patch for slightly faster latch response times.
2021-06-27 Reworked when inputs are loaded from flash, and changed latch/clock response behavior to properly handle overreads and latches without all 8 clocks.
2021-06-28 Cleaned up commented/debug code.
2021-07-12 Added NES vizboard input display. Reorganized hardware directories. Changed license to the more suitable CERN OHL-W
2021-07-16 Revised PCB design again.
2021-07-18 Fixed firmware bug where the device was wrongly initializing the TAS at boot, instead of at start of playback.
2021-07-18 Reorganized firmware code into console-specific include files.
2021-08-01 Partially working. SPI to FLASH has severe issues on PCB
2021-09-01 More redesign progress
2021-09-19 More design changes
2021-09-21 New firmware confirmed to be able to program FLASH and verified using mass dump.
2021-09-21 Finalized new prototype designs.
2021-09-22 Added A2600 Joystick input display pcb.
2021-10-03 Version update and minor joystick board changes.
2021-10-03 Reorganized pcb files
2021-10-03 Fixed strobe pinout to match hardware, and now clears all input displays at startup.
2021-10-03 Fixed inter-board communication bug (TRISE[2] set incorrectly on MCU-Play)
2021-10-03 Updated README.
2021-10-03 Added image to README.
2021-10-04 Updated pinout spreadsheet to reflect current design.
2021-10-20 Added new inter-MCU communication protocol with QoL firmware changes.
2021-10-20 Reorganized ISR code into separate files and renamed main loop.
2021-10-20 Moved replay usb command handling to an ISR. Removed unused file from viz source.
2021-10-20 Added reset command (can be used to stop a replay)
2022-05-04 Atari 2600 and beginner Genesis work; reorganized firmware.
2022-06-09 Progress toward replacing pinheaders with D-Sub connector.

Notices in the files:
README.md:
License: CERN OHL-W-V2
hardware/pictas-pcb/pictas.kicad_pcb:
Licensed under CERN-OHL-W-2.0
